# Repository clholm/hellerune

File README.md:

# hellerune
a CD4049UBE overdrive (similar to the Greedtone or Red Llama overdrives)

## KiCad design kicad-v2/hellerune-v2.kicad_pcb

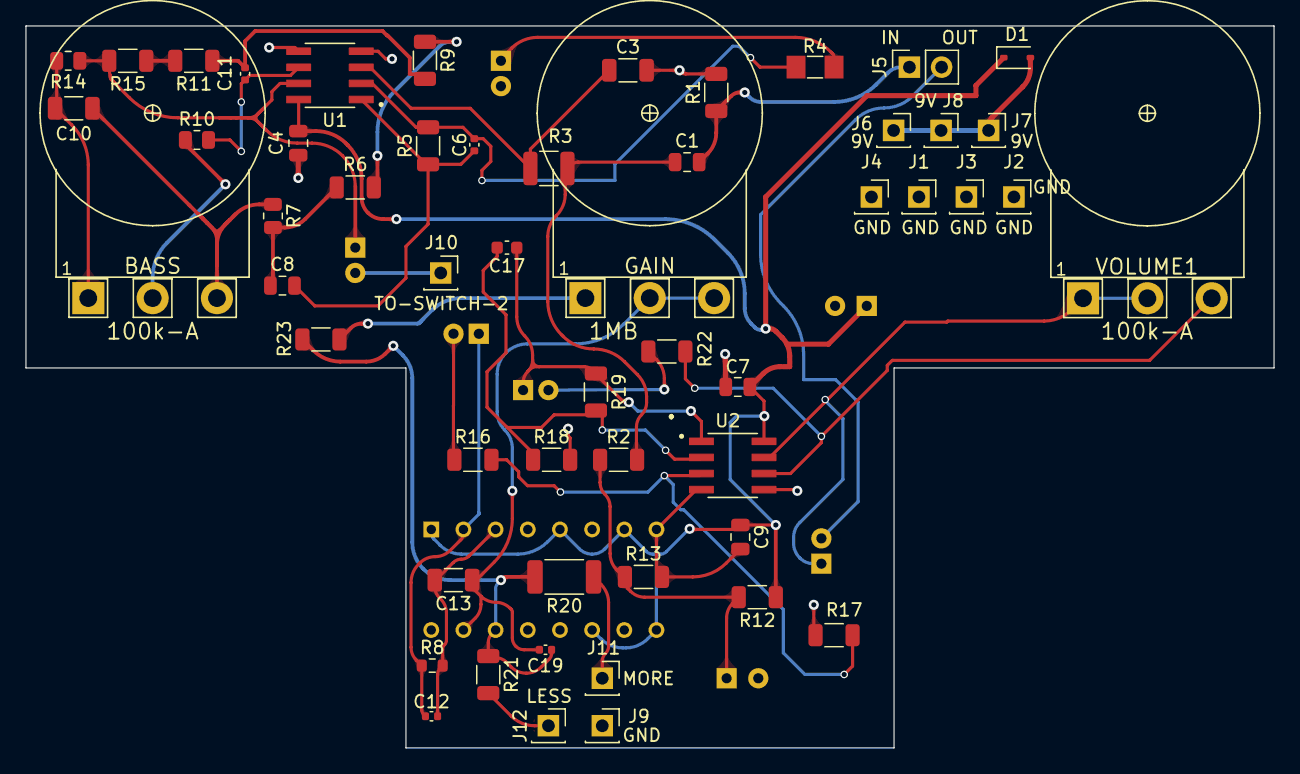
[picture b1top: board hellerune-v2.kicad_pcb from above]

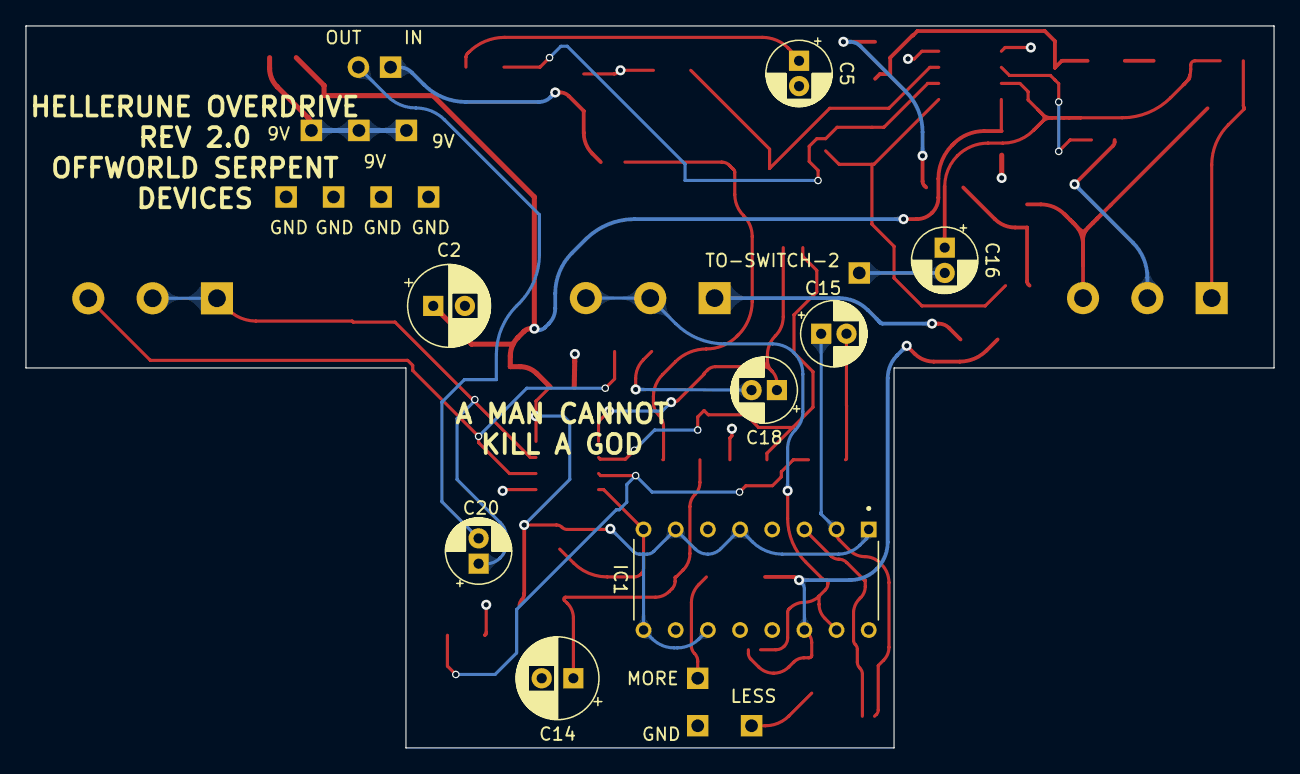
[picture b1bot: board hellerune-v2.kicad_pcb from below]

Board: 4 copper layers, 98.5 x 57.0 mm, 62 parts (8 on the bottom side), 35 nets.

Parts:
BASS: 100k-A; 16MM_T.MOUNT
C1, C4, C7, C9: 10nF; C_0805_2012Metric
C2, C14: 100uF; CP_Radial_D6.3mm_P2.50mm
C3: 4.7nF; C_1206_3216Metric
C5, C15, C16, C18, C20: 4.7uF-bi; CP_Radial_D5.0mm_P2.00mm
C6: 1nF; C_0402_1005Metric
C8: 22nF; C_0805_2012Metric
C10, C13: 47nF; C_1206_3216Metric
C11: 560pF; C_0402_1005Metric
C12, C19: 10pF; C_0402_1005Metric
C17: 3.3nF; C_0603_1608Metric
D1: 1N5817; D_SOD-323
GAIN: 1MB; 16MM_T.MOUNT
IC1: CD4049UBE; DIP794W45P254L1930H508Q16
J1: GND1; PinSocket_1x01_P2.54mm_Vertical
J2: GND2; PinSocket_1x01_P2.54mm_Vertical
J3: GND3; PinSocket_1x01_P2.54mm_Vertical
J4: GND4; PinSocket_1x01_P2.54mm_Vertical
J5: Conn_01x02_Female; PinSocket_1x02_P2.54mm_Vertical
J6: 9VIN; PinSocket_1x01_P2.54mm_Vertical
J7: 9VOUT1; PinSocket_1x01_P2.54mm_Vertical
J8: 9VOUT2; PinSocket_1x01_P2.54mm_Vertical
J9: GND5; PinSocket_1x01_P2.54mm_Vertical
J10: SWITCHY-2-B-OUT; PinSocket_1x01_P2.54mm_Vertical
J11: SWITCHY-2-B-IN-R2; PinSocket_1x01_P2.54mm_Vertical
J12: SWITCHY-2-B-IN-R1; PinSocket_1x01_P2.54mm_Vertical
R1, R2, R17: 2.2M; R_1206_3216Metric
R3: 1k; R_1210_3225Metric
R4: 2.2k; R_MiniMELF_MMA-0204
R5, R9, R11, R16: 10k; R_1206_3216Metric
R6, R15: 47k; R_1206_3216Metric
R7, R10, R14: 22k; R_0805_2012Metric
R8: 10M; R_0603_1608Metric
R12, R13, R21, R22, R23: 100k; R_1206_3216Metric
R18, R19: 200k; R_1206_3216Metric
R20: 270R; R_2010_5025Metric
U1, U2: OPA1678; OPA1678-SOIC8
VOLUME1: 100k-A; 16MM_T.MOUNT

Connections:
9V: D1.2 (A), J6.1, J7.1, J8.1
CD-VCC: C2.1, C4.1, C7.1, C9.1, D1.1 (K), IC1.1 (VCC), IC1.5 (B), IC1.7 (C), IC1.9 (D), IC1.11 (E), R12.1, U1.8 (V+), U2.8 (V+)
Earth: C2.2, C3.2, C4.2, C5.2, C7.2, C9.2, C14.2, IC1.8 (VSS), J1.1, J2.1, J3.1, J4.1, J9.1, R1.2, R13.2, R18.2, U1.4 (V-), U2.4 (V-)
INPUT: C1.2, J5.1, R1.1
unnamed: BASS.1, C10.1, R14.2
unnamed: BASS.2, R10.1
unnamed: BASS.3, C10.2, R7.1
unnamed: C1.1, R2.2, R3.2
unnamed: C5.1, R4.2
unnamed: C6.1, C8.2, R5.1, U1.1
unnamed: C8.1, R6.1, R7.2
unnamed: C11.2, R9.2, R11.1
unnamed: C15.2, R16.1
unnamed: C16.1, R14.1, R15.2, U1.7
unnamed: C17.1, C18.1, R19.1, U2.1
unnamed: C18.2, R22.2
unnamed: C20.1, U2.7, VOLUME1.1, VOLUME1.2
unnamed: GAIN.1, R23.1
unnamed: C12.2, C13.2, IC1.3 (A), R8.2
unnamed: C19.2, IC1.14 (F), R20.2, R21.1, R23.2
unnamed: C12.1, C15.1, IC1.2 (G), R8.1
unnamed: C13.1, C19.1, GAIN.2, GAIN.3, IC1.15 (L)
unnamed: C16.2, J10.1
unnamed: J11.1, R20.1
unnamed: J12.1, R21.2
unnamed: R6.2, R9.1
unnamed: R11.2, R15.1
unnamed: C3.1, R3.1, U1.3 (+)
unnamed: C6.2, R4.1, R5.2, U1.2 (-)
unnamed: C11.1, R10.2, U1.6 (-)
unnamed: R16.2, R17.2, U2.3 (+)
unnamed: C17.2, R18.1, R19.2, U2.2 (-)
unnamed: R22.1, U2.6 (-), VOLUME1.3
OUTPUT: C20.2, J5.2
VREF: C14.1, R2.1, R12.2, R13.1, R17.1, U1.5 (+), U2.5 (+)

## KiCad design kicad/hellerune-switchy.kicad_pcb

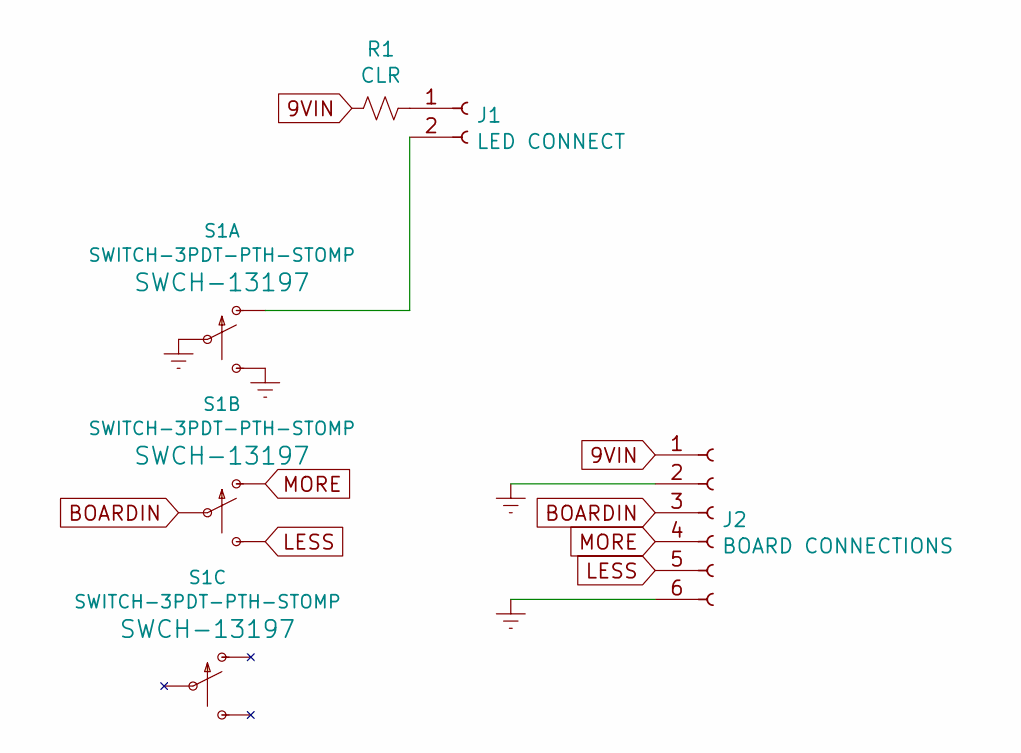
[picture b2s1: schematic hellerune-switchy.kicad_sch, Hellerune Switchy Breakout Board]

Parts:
J1: LED CONNECT; PinHeader_1x02_P2.54mm_Vertical
J2: BOARD CONNECTIONS; PinHeader_1x06_P2.54mm_Vertical
R1: CLR; 0.3_resistor
S1: SWITCH-3PDT-PTH-STOMP; STOMP_SWITCH_3PDT_TAIWAY_LOW_PROFILE

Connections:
9VIN: J2.1, R1.2
BOARDIN: J2.3, S1.P$5
Earth: J2.2, J2.6, S1.P$2, S1.P$3 (S)
LESS: J2.5, S1.P$6 (S)
MORE: J2.4, S1.P$4 (O)
unnamed: J1.1, R1.1
unnamed: J1.2, S1.P$1 (O)

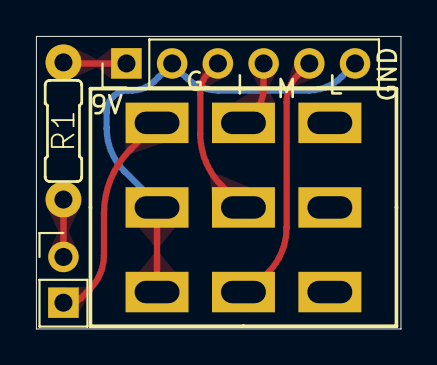
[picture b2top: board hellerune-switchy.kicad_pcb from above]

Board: 2 copper layers, 20.2 x 16.2 mm, 4 parts (0 on the bottom side), 7 nets.

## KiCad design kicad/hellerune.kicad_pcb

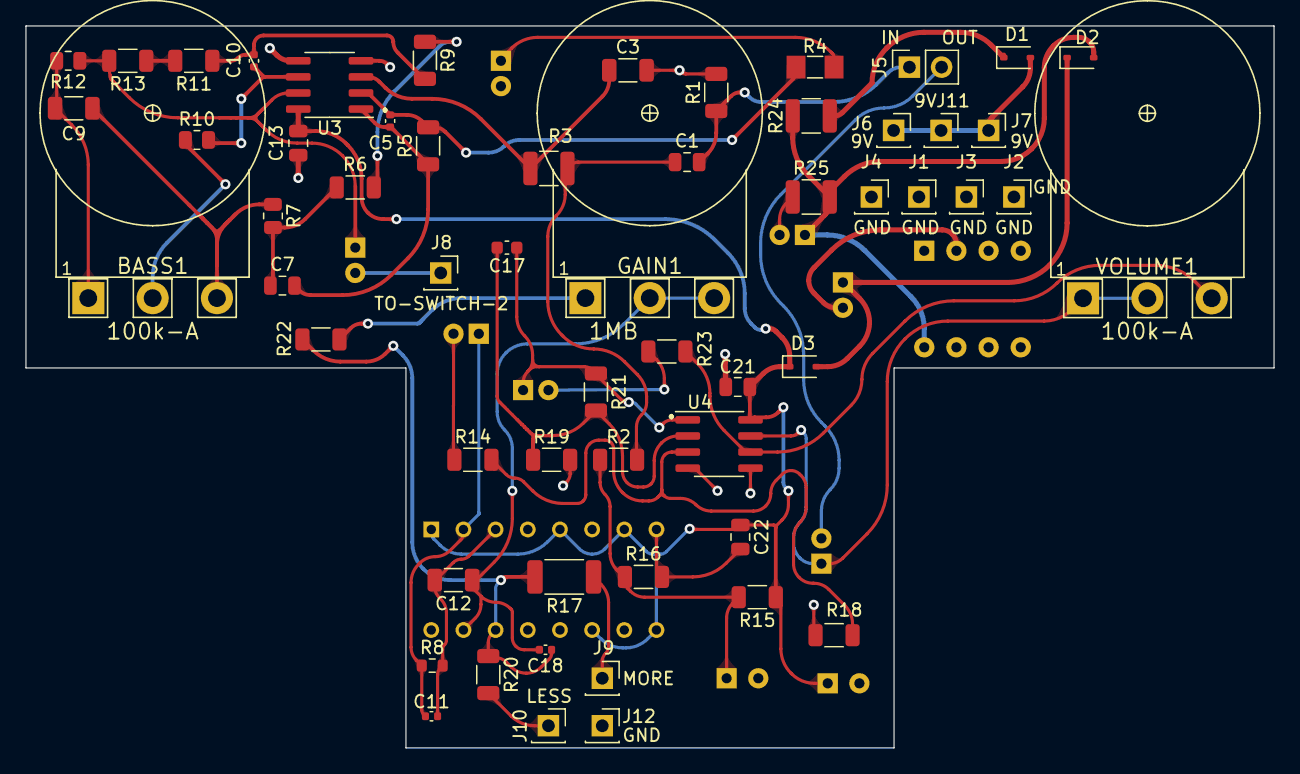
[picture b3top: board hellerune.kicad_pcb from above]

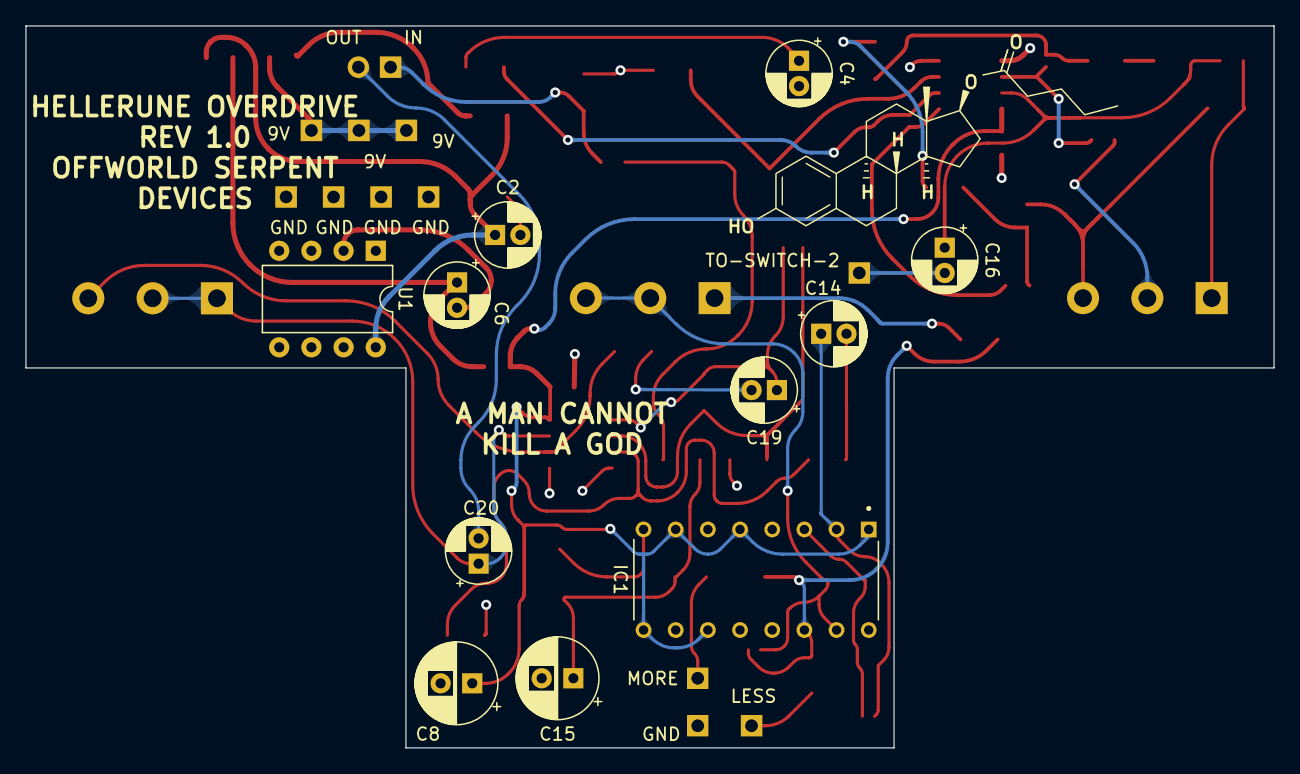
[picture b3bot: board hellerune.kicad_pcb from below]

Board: 4 copper layers, 98.5 x 57.0 mm, 70 parts (12 on the bottom side), 39 nets.

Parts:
 : est-comic
BASS1: 100k-A; 16MM_T.MOUNT
C1, C13, C21, C22: 10nF; C_0805_2012Metric
C2: 2.2uF; CP_Radial_D5.0mm_P2.00mm
C3: 4.7nF; C_1206_3216Metric
C4, C14, C16, C19, C20: 4.7uF-bi; CP_Radial_D5.0mm_P2.00mm
C5: 1nF; C_0402_1005Metric
C6: 10uF; CP_Radial_D5.0mm_P2.00mm
C7: 22nF; C_0805_2012Metric
C8, C15: 100uF; CP_Radial_D6.3mm_P2.50mm
C9, C12: 47nF; C_1206_3216Metric
C10: 560pF; C_0402_1005Metric
C11, C18: 10pF; C_0402_1005Metric
C17: 3.3nF; C_0603_1608Metric
D1, D2, D3: 1N4001; D_SOD-323
GAIN1: 1MB; 16MM_T.MOUNT
IC1: CD4049UBE; DIP794W45P254L1930H508Q16
J1: GND1; PinSocket_1x01_P2.54mm_Vertical
J2: GND2; PinSocket_1x01_P2.54mm_Vertical
J3: GND3; PinSocket_1x01_P2.54mm_Vertical
J4: GND4; PinSocket_1x01_P2.54mm_Vertical
J5: Conn_01x02_Female; PinSocket_1x02_P2.54mm_Vertical
J6: 9VIN; PinSocket_1x01_P2.54mm_Vertical
J7: 9VOUT1; PinSocket_1x01_P2.54mm_Vertical
J8: SWITCHY-2-B-OUT; PinSocket_1x01_P2.54mm_Vertical
J9: SWITCHY-2-B-IN-R2; PinSocket_1x01_P2.54mm_Vertical
J10: SWITCHY-2-B-IN-R1; PinSocket_1x01_P2.54mm_Vertical
J11: 9VOUT2; PinSocket_1x01_P2.54mm_Vertical
J12: GND5; PinSocket_1x01_P2.54mm_Vertical
R1, R2, R18: 2.2M; R_1206_3216Metric
R3, R24: 1k; R_1210_3225Metric
R4: 2.2k; R_MiniMELF_MMA-0204
R5, R9, R11, R14: 10k; R_1206_3216Metric
R6, R13: 47k; R_1206_3216Metric
R7, R10, R12: 22k; R_0805_2012Metric
R8: 10M; R_0603_1608Metric
R15, R16, R20, R22, R23: 100k; R_1206_3216Metric
R17: 270R; R_2010_5025Metric
R19, R21: 200k; R_1206_3216Metric
R25: 3k; R_1210_3225Metric
U1: LT1054; DIP-8_W7.62mm
U3, U4: TL072; SOIC-8_3.9x4.9mm_P1.27mm
VOLUME1: 100k-A; 16MM_T.MOUNT

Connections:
9V: D1.2 (A), J6.1, J7.1, J11.1
CD-VCC: C8.1, C13.1, C21.1, C22.1, D3.1 (K), IC1.1 (VCC), IC1.5 (B), IC1.7 (C), IC1.9 (D), IC1.11 (E), R15.1, U3.8 (V+), U4.8 (V+)
Earth: C2.2, C3.2, C4.2, C8.2, C13.2, C15.2, C21.2, C22.2, IC1.8 (VSS), J1.1, J2.1, J3.1, J4.1, J12.1, R1.2, R16.2, R19.2, R25.1, U1.3 (GND), U1.5 (-VOUT), U3.4 (V-), U4.4 (V-)
INPUT: C1.2, J5.1, R1.1
unnamed: BASS1.1, C9.1, R12.2
unnamed: BASS1.2, R10.1
unnamed: BASS1.3, C9.2, R7.1
unnamed: C1.1, R2.2, R3.2
unnamed: C4.1, R4.2
unnamed: C5.1, C7.2, R5.1, U3.1
unnamed: C7.1, R6.1, R7.2
unnamed: C10.2, R9.2, R11.1
unnamed: C14.2, R14.1
unnamed: C16.1, R12.1, R13.2, U3.7
unnamed: C17.1, C19.1, R21.1, U4.1
unnamed: C19.2, R23.2
unnamed: C20.1, U4.7, VOLUME1.1, VOLUME1.2
unnamed: D1.1 (K), R24.1
unnamed: C2.1, D2.2 (A), R24.2, R25.2, U1.8 (V+)
unnamed: C6.1, D2.1 (K), D3.2 (A)
unnamed: GAIN1.1, R22.1
unnamed: C11.2, C12.2, IC1.3 (A), R8.2
unnamed: C18.2, IC1.14 (F), R17.2, R20.1, R22.2
unnamed: C11.1, C14.1, IC1.2 (G), R8.1
unnamed: C12.1, C18.1, GAIN1.2, GAIN1.3, IC1.15 (L)
unnamed: C16.2, J8.1
unnamed: J9.1, R17.1
unnamed: J10.1, R20.2
unnamed: R6.2, R9.1
unnamed: R11.2, R13.1
unnamed: C6.2, U1.2 (CAP+)
unnamed: C3.1, R3.1, U3.3 (+)
unnamed: C5.2, R4.1, R5.2, U3.2 (-)
unnamed: C10.1, R10.2, U3.6 (-)
unnamed: R14.2, R18.2, U4.3 (+)
unnamed: C17.2, R19.1, R21.2, U4.2 (-)
unnamed: R23.1, U4.6 (-), VOLUME1.3
OUTPUT: C20.2, J5.2
VREF: C15.1, R2.1, R15.2, R16.1, R18.1, U3.5 (+), U4.5 (+)

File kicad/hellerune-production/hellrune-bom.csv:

Designator,Footprint,Quantity,Value,LCSC Part #
"C1, C13, C21, C22",805,4,10nF,C441760
C10,402,1,560pF,C295992
"C11, C18",402,2,10pF,C268017
"C12, C9",1206,2,47nF,C21812
C17,603,1,3.3nF,C77036
C3,1206,1,4.7nF,C393168
C5,402,1,1nF,C113780
C7,805,1,22nF,C77069
"D1, D2, D3",D_SOD-323,3,1N4001,C2898400
"R1, R18, R2",1206,3,2.2M,C171070
"R10, R12, R7",805,3,22k,C186285
"R11, R14, R5, R9",1206,4,10k,C416174
"R13, R6",1206,2,47k,C844663
"R15, R16, R20, R22, R23",1206,5,100k,C137393
R17,2010,1,270R,C138230
"R19, R21",1206,2,200k,C416177
"R24, R3",1210,2,1k,C83144
R25,1210,1,3k,C326796
R4,R_MiniMELF_MMA-0204,1,2.2k,C1884620
R8,603,1,10M,C103202
"U3, U4",SOIC-8_3.9x4.9mm_P1.27mm,2,TL072,C6962

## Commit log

2023-05-22 first commit, started schematic
2023-05-30 schematic complete
2023-05-30 corrected llama capitalization
2023-05-31 updated schematic
2023-06-03 updated footprints
2023-07-05 began PCB, traces
2023-07-05 pcb draft complete
2023-07-06 finished pcb, commit before making wavy
2023-07-07 pcb rev 1
2023-07-18 pick and place files created
2023-07-23 pcb for second switch
2023-07-27 gerber files for the second switch breakout board
2023-08-03 v2 started
